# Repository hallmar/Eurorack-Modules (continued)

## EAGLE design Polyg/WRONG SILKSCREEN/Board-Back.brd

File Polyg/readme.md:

>ATTENTION BUILDERS THAT GOT THE FIRST BATCH OF 10 PCB'S(you can tell if they're part of that batch if they have no 'Version 1.1' written on them), THERE WAS A MAJOR ERROR IN THE SILKSCREEN DUE TO ME BEING AN IDIOT, SEE THE FOLDER CALLED 'WRONG SILKSCREEN' AND REFER TO THE 'BUILD MANUAL - WRONG SILKSCREEN' FOR CORRECT COMPONENT NUMBERING IN THE SCHEMATIC AND BOARD FILES FOR YOUR PCB VERSION

# Polyg 8-Voice Midi synth

# THIS PROJECT IS DISCONTINUED IN FAVOR OF V2 

[Youtube demo](https://www.youtube.com/watch?v=QhJZFhLLbBc&feature=youtu.be)

8 Voice polyphonic synthesizer with selectable Karplus strong(8 voice plucky string synth) or a 8 voice FM synth with square,sine,triangle and sawtooth. It has a basic FM(techincally Phase Modulation, like the DX7) with one Modulator. 
There's an index knob to set the ratio, decay for the operator and the amount of FM applied.

Current hardware uses a high quality 16bit/44.1kHz DAC(CD4334).

It has MIDI IN and MIDI OUT/THRU. It uses the Arturia Standard for DIN to stereo jack, so type B midi.
You can find adapters in almost every synthstore now. 

## Where/how to order
I won't have any PCB's in stock any time soon. This project is pretty much abandoned in favor of v2.
## Designed With

* Eagle CAD
* Arduino IDE
* Audio System Design Tool for Teensy Audio Library

## Versioning
* 1.0 - [Hardware] Original PCB batch with wrong silkscreen
* 1.1 - [Hardware] Current version of PCBs
* 1.0 - [Software] Original software release
## Authors

* **Hallmar Gauti Halldórsson** 

## License
Hardware: cc-by-sa-3.0

Software: MIT license

But if you want to sell or do something with the software or hardware then it'd be nice to include my name and link to my Github somewhere :)

## Acknowledgments
Alot of the inspiration for this project came from the [String Theory](https://makesynthsnotwar.com/modules/stringtheory/) eurorack module by Make Synths Not War.
The original String Theory was programmed by [Jan Ostman](https://janostman.wordpress.com).

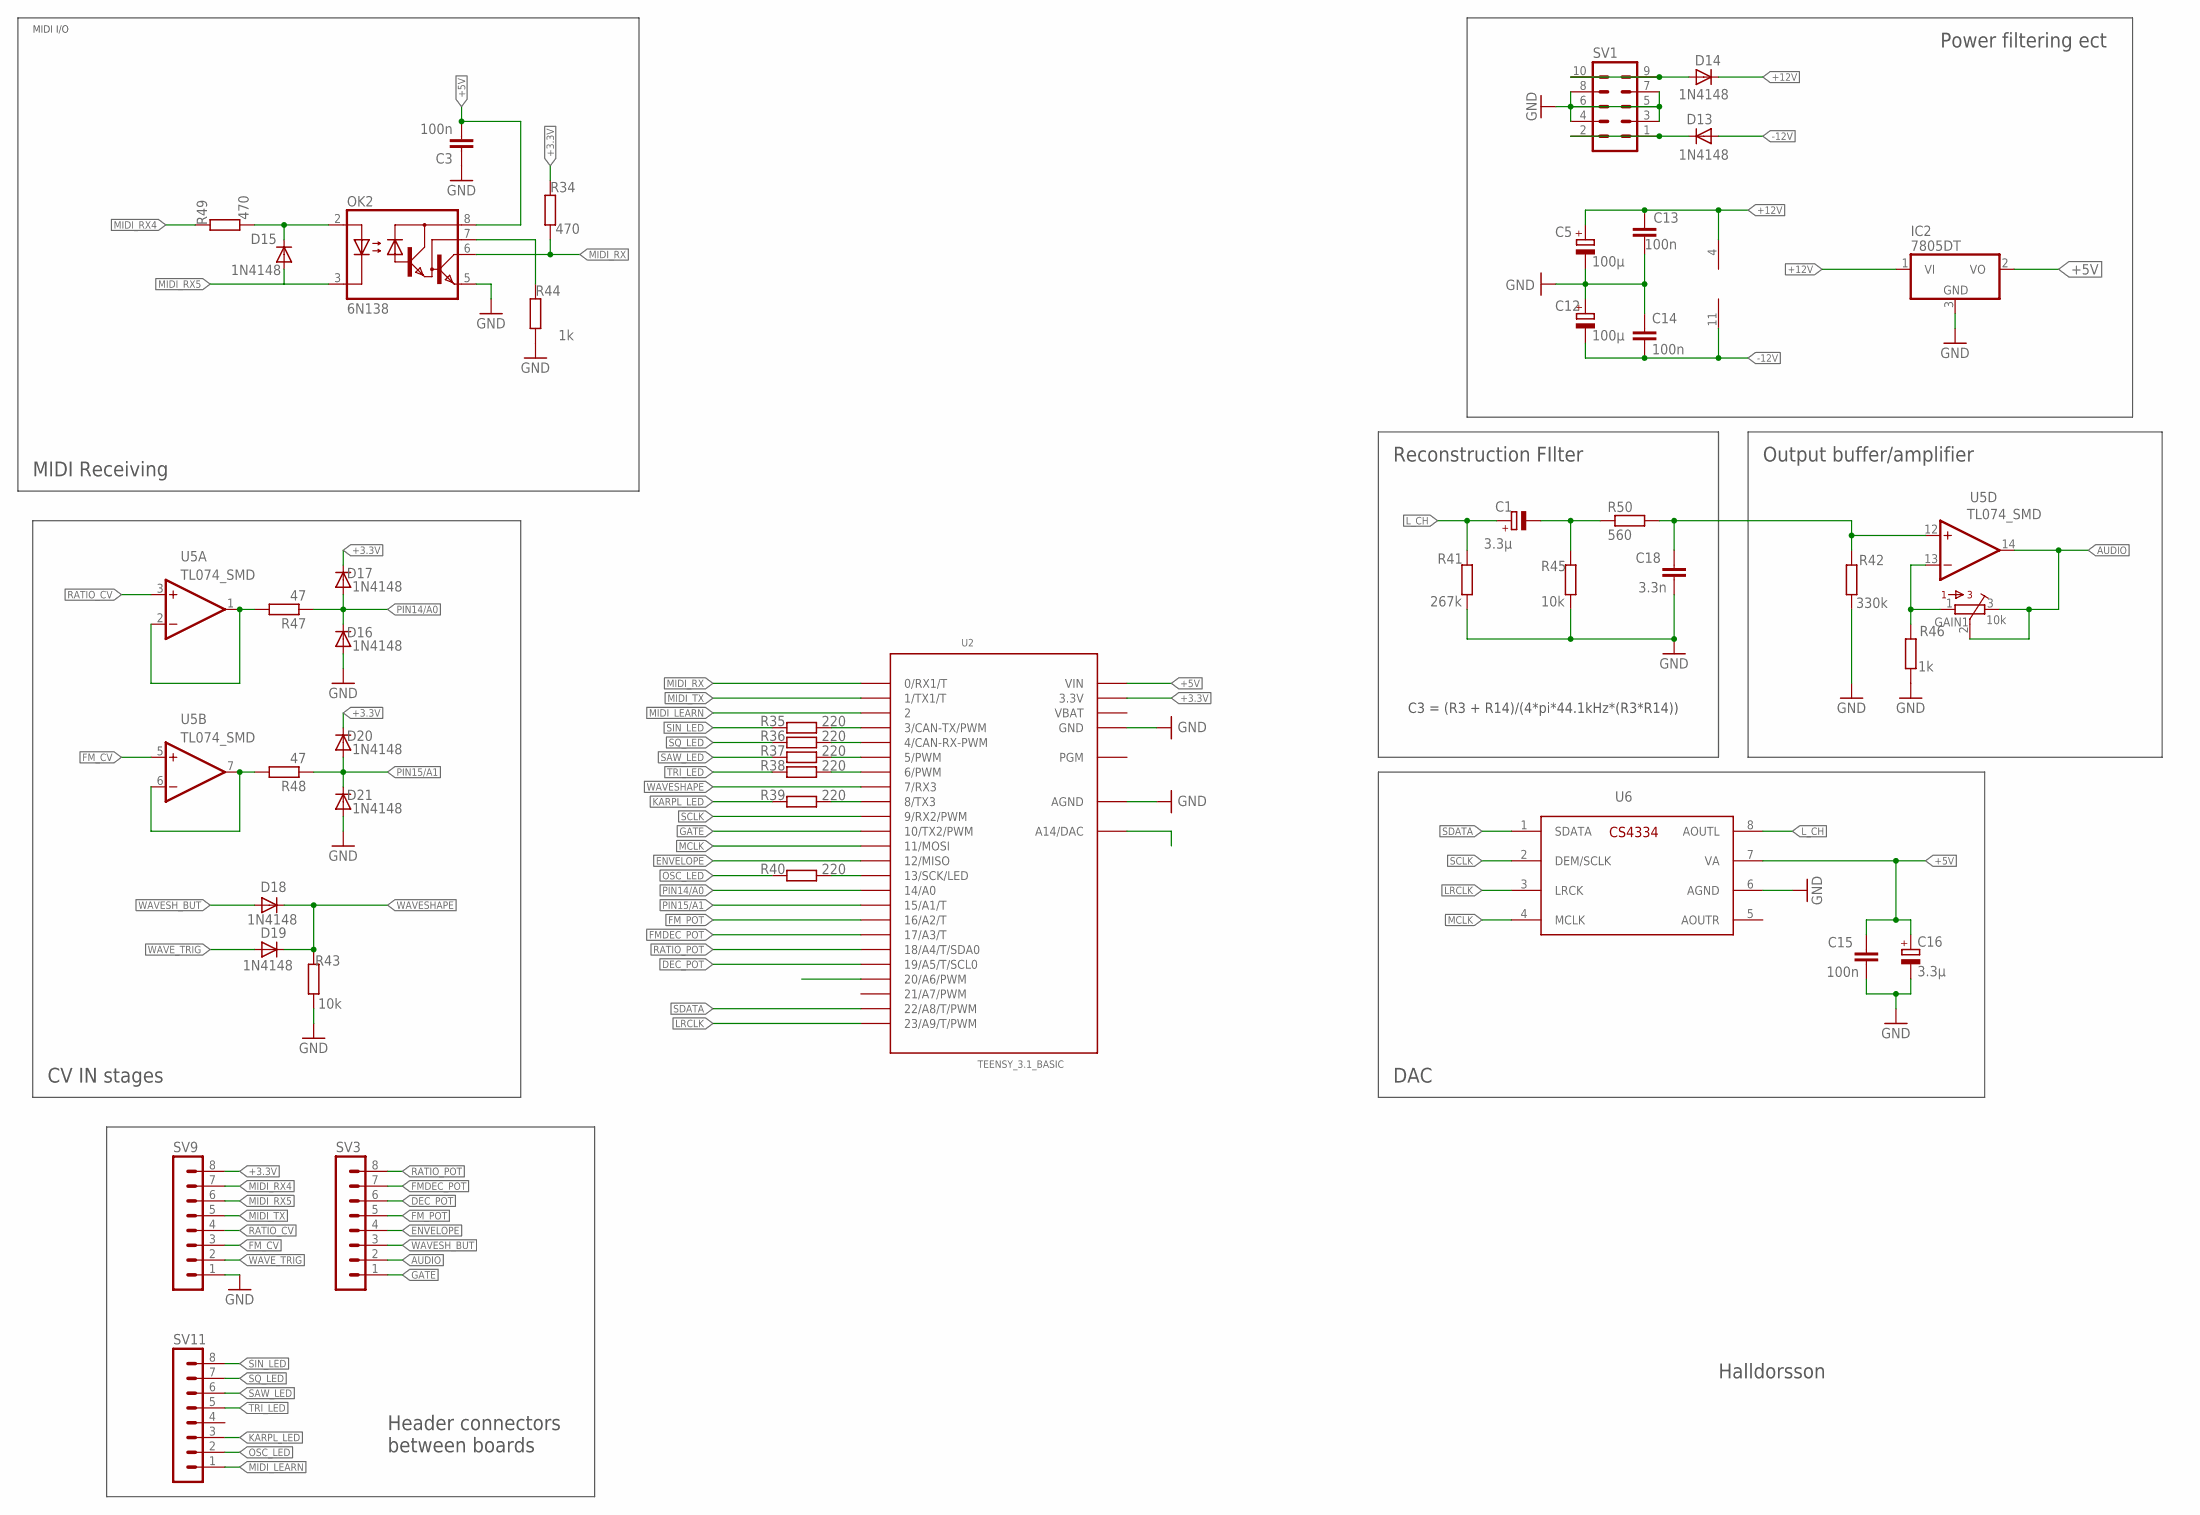
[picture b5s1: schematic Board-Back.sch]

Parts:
C1: 3.3µ; 153CLV-0405
C3, C13, C14, C15: 100n; C1206
C5, C12: 100µ; E5-6
C16: 3.3µ; 153CLV-0505
C18: 3.3n; C1206
D13, D14, D15, D16, D17, D18, D19, D20, D21: 1N4148; DO35-7
GAIN1: 10k; BOURNS_3362P_TRIMMER
IC2: 7805DT; TO252
OK2: 6N138; DIL08
R34, R49: 470; M1206
R35, R36, R37, R38, R39, R40: 220; M1206
R41: 267k; M1206
R42: 330k; M1206
R43, R45: 10k; M1206
R44, R46: 1k; M1206
R47, R48: 47; M1206
R50: 560; M1206
SV1: 10PIN_BACKSIDE
SV3, SV9, SV11: MA08-1
U2: TEENSY_3.1_BASIC
U5: TL074_SMD; SO14
U6: CS4334; SOIC127P600X175-8N

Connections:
+3.3V: D17.C, D20.C, R34.2, SV9.8, U2.3.3V, U2.3.3V1 (3.3V)
+5V: C3.2, C15.1, C16.+, IC2.2 (VO), OK2.8 (VCC), U2.VIN, U6.7 (VA)
+12V: C5.+, C13.1, D14.C, IC2.1 (VI), U5.4 (V+)
-12V: C12.-, C14.2, D13.A, U5.11 (V-)
AUDIO: GAIN1.2, GAIN1.3, SV3.2, U5.14 (OUT)
DEC_POT: SV3.6, U2.19/A5 (19/A5/T/SCL0)
ENVELOPE: SV3.4, U2.12 (12/MISO)
FMDEC_POT: SV3.7, U2.17/A3 (17/A3/T)
FM_CV: SV9.3, U5.5 (+IN)
FM_POT: SV3.5, U2.16/A2 (16/A2/T)
GATE: SV3.1, U2.10 (10/TX2/PWM)
GND: C3.1, C5.-, C12.+, C13.2, C14.1, C15.2, C16.-, C18.2, D16.A, D21.A, IC2.3 (GND), OK2.5 (GND), R41.2, R42.2, R43.1, R44.1, R45.2, R46.2, SV1.3, SV1.4, SV1.5, SV1.6, SV1.7, SV1.8, SV9.1, U2.AGND, U2.GND, U2.GND1 (GND), U6.6 (AGND)
KARPL_LED: R39.2, SV11.3
LRCLK: U2.23/A9 (23/A9/T/PWM), U6.3 (LRCK)
L_CH: C1.+, R41.1, U6.8 (AOUTL)
MCLK: U2.11 (11/MOSI), U6.4 (MCLK)
MIDI_LEARN: SV11.1, U2.2
MIDI_RX: OK2.6 (VO), R34.1, U2.0 (0/RX1/T)
MIDI_RX4: R49.2, SV9.7
MIDI_RX5: D15.A, OK2.3 (C), SV9.6
MIDI_TX: SV9.5, U2.1 (1/TX1/T)
unnamed: C1.-, R45.1, R50.1
unnamed: D13.C, SV1.1, SV1.2
unnamed: D15.C, OK2.2 (A), R49.1
unnamed: OK2.7 (VB), R44.2
unnamed: GAIN1.1, R46.1, U5.13 (-IN)
unnamed: D14.A, SV1.9, SV1.10
unnamed: R40.1, U2.13 (13/SCK/LED)
unnamed: C18.1, R42.1, R50.2, U5.12 (+IN)
unnamed: R35.1, U2.3 (3/CAN-TX/PWM)
unnamed: R36.1, U2.4 (4/CAN-RX-PWM)
unnamed: R37.1, U2.5 (5/PWM)
unnamed: R48.2, U5.6 (-IN), U5.7 (OUT)
unnamed: R47.2, U5.1 (OUT), U5.2 (-IN)
unnamed: R38.1, U2.6 (6/PWM)
unnamed: R39.1, U2.8 (8/TX3)
OSC_LED: R40.2, SV11.2
PIN14/A0: D16.C, D17.A, R47.1, U2.14/A0
PIN15/A1: D20.A, D21.C, R48.1, U2.15/A1 (15/A1/T)
RATIO_CV: SV9.4, U5.3 (+IN)
RATIO_POT: SV3.8, U2.18/A4 (18/A4/T/SDA0)
SAW_LED: R37.2, SV11.6
SCLK: U2.9 (9/RX2/PWM), U6.2 (DEM/SCLK)
SDATA: U2.22/A8 (22/A8/T/PWM), U6.1 (SDATA)
SIN_LED: R35.2, SV11.8
SQ_LED: R36.2, SV11.7
TRI_LED: R38.2, SV11.5
VBAT: U2.VBAT
WAVESHAPE: D18.C, D19.C, R43.2, U2.7 (7/RX3)
WAVESH_BUT: D18.A, SV3.3
WAVE_TRIG: D19.A, SV9.2

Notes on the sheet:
MIDI I/O
Halldorsson
DAC
Reconstruction FIlter
CV IN stages
Header connectors between boards
MIDI Receiving
Power filtering ect
Output buffer/amplifier
C3 = (R3 + R14)/(4*pi*44.1kHz*(R3*R14))

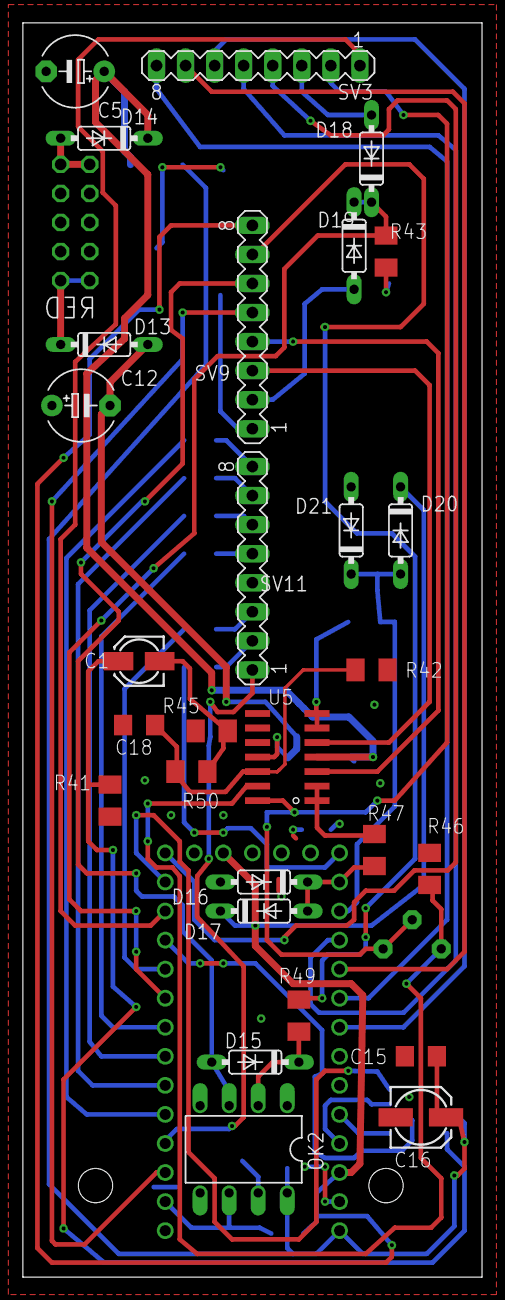
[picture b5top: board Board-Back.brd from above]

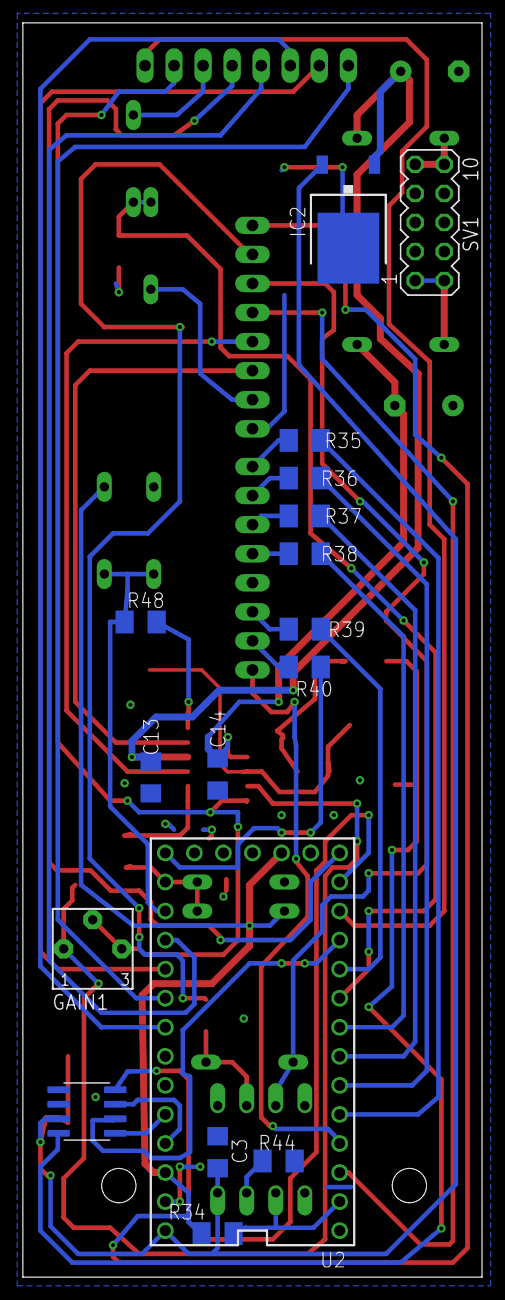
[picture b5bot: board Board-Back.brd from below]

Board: 2 copper layers, 40.1 x 109.7 mm, 45 parts (16 on the bottom side), 50 nets.

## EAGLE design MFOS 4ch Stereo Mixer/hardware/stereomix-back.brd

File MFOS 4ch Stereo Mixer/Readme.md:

# Music From Outer Space 4 channel Stereo mixer 
It's simple.
It's a 4 channel stereo in and one stereo out mixer.
Has 1 attenuator per channel, the left jack is normalled to the right(if you only plug a jack into the left then the signal at the left jack is passed to the right channel too).

[original schematic](http://musicfromouterspace.com/analogsynth_new/HOT_TIPS/PDF/simple_stereo_summer_assembly.pdf)

## Where/how to order
Not selling any PCB's for this one. It's only for open source/documentation purposes.

## Designed With

* Eagle CAD

## Versioning

## Authors

* PCB design by **Hallmar Gauti Halldórsson** 
* Original Schematic design by the late **Ray Wilson of Music From Outer Space**

## License
Hardware: cc-by-sa-3.0

## Acknowledgments
The design of the circuit was completely done by the great Ray Wilson of [Music From Outer Space](http://musicfromouterspace.com).
I merely designed the frontpanel and PCB for it for Eurorack. Here is the [original schematic](http://musicfromouterspace.com/analogsynth_new/HOT_TIPS/PDF/simple_stereo_summer_assembly.pdf)

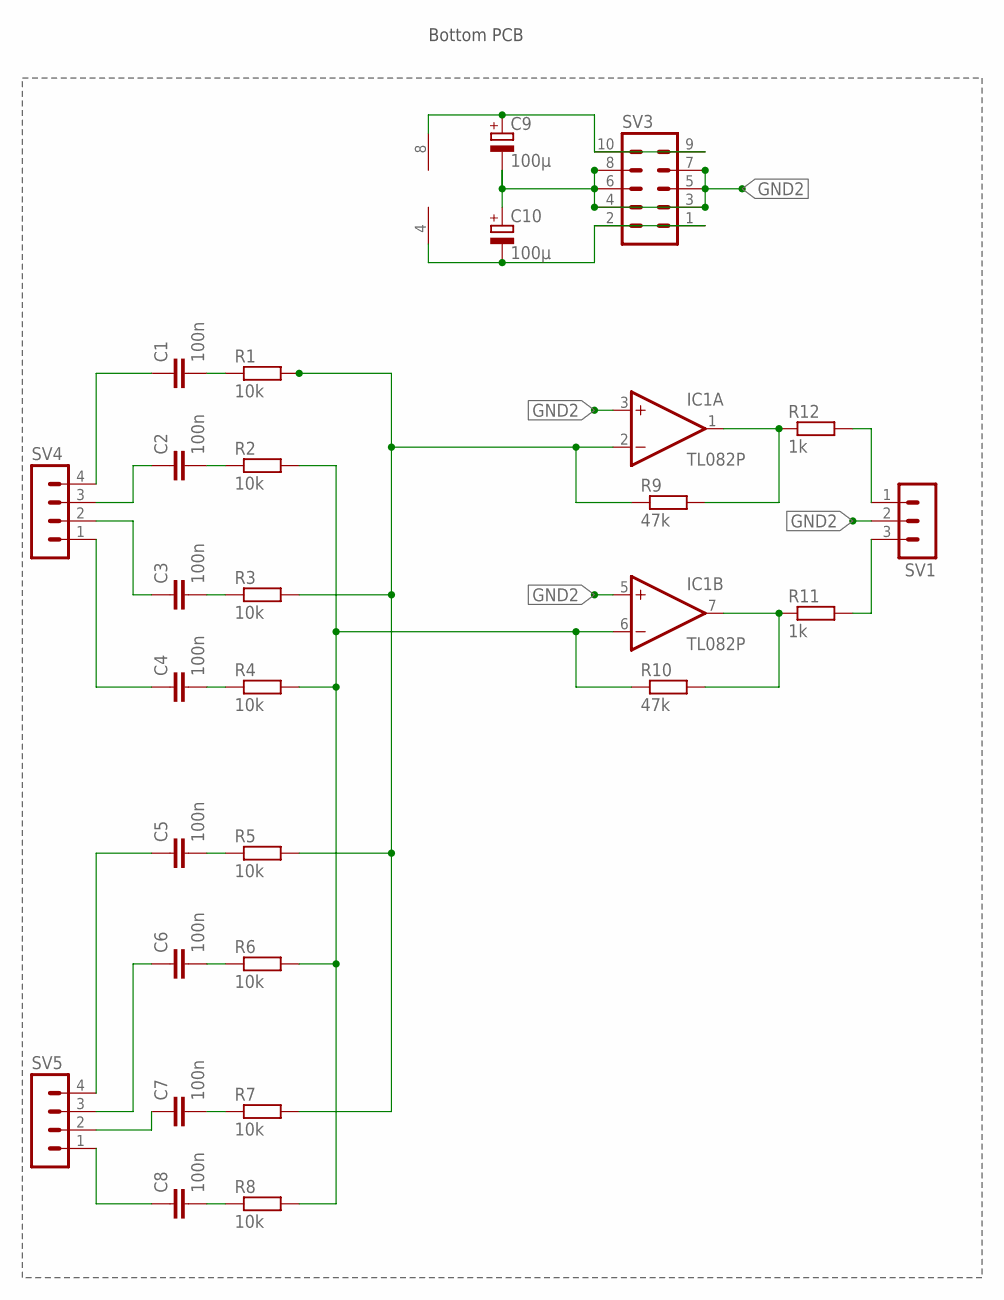
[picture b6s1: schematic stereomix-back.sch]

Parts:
C1, C2, C3, C4, C5, C6, C7, C8: 100n; C050-024X044
C9: 100µ; E2,5-6
C10: 100µ; E2,5-6E
IC1: TL082P; DIL08
R1, R2, R3, R4, R5, R6, R7, R8: 10k; 0204/7
R9, R10: 47k; 0204/7
R11, R12: 1k; 0204/7
SV1: MA03-1
SV3: MA05-2
SV4, SV5: MA04-1

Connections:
GND2: C9.-, C10.+, IC1.3 (+IN), IC1.5 (+IN), SV1.2, SV3.3, SV3.4, SV3.5, SV3.6, SV3.7, SV3.8
unnamed: IC1.2 (-IN), R1.2, R3.2, R5.2, R7.2, R9.1
unnamed: IC1.1 (OUT), R9.2, R12.1
unnamed: IC1.7 (OUT), R10.2, R11.1
unnamed: IC1.6 (-IN), R2.2, R4.2, R6.2, R8.2, R10.1
unnamed: R12.2, SV1.1
unnamed: C1.2, R1.1
unnamed: C2.2, R2.1
unnamed: C3.2, R3.1
unnamed: C4.2, R4.1
unnamed: C5.2, R5.1
unnamed: C6.2, R6.1
unnamed: C7.2, R7.1
unnamed: C8.2, R8.1
unnamed: R11.2, SV1.3
unnamed: C9.+, IC1.8 (V+), SV3.9, SV3.10
unnamed: C10.-, IC1.4 (V-), SV3.1, SV3.2
unnamed: C8.1, SV5.1
unnamed: C7.1, SV5.2
unnamed: C6.1, SV5.3
unnamed: C5.1, SV5.4
unnamed: C4.1, SV4.1
unnamed: C3.1, SV4.2
unnamed: C2.1, SV4.3
unnamed: C1.1, SV4.4

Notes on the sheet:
Bottom PCB

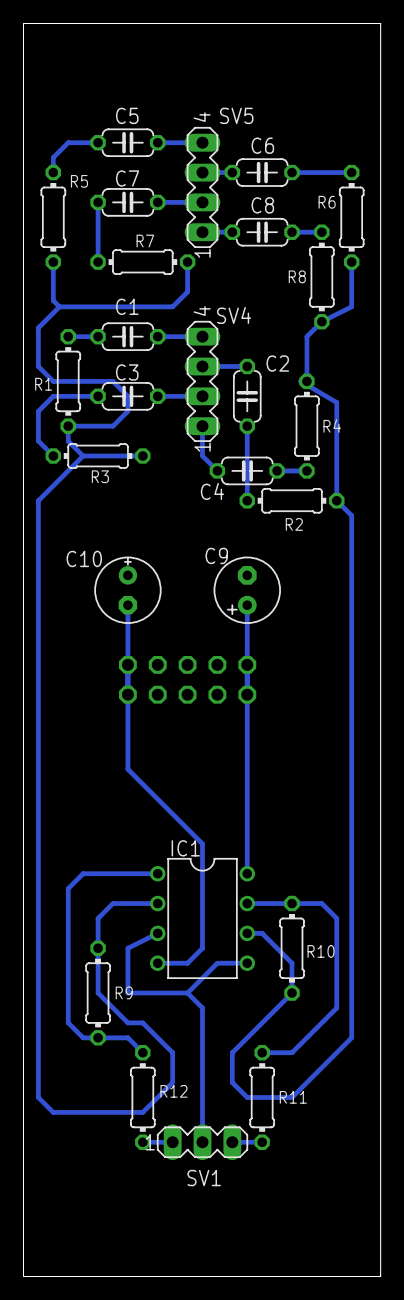
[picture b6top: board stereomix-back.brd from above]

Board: 2 copper layers, 30.4 x 106.7 mm, 27 parts (1 on the bottom side), 25 nets.

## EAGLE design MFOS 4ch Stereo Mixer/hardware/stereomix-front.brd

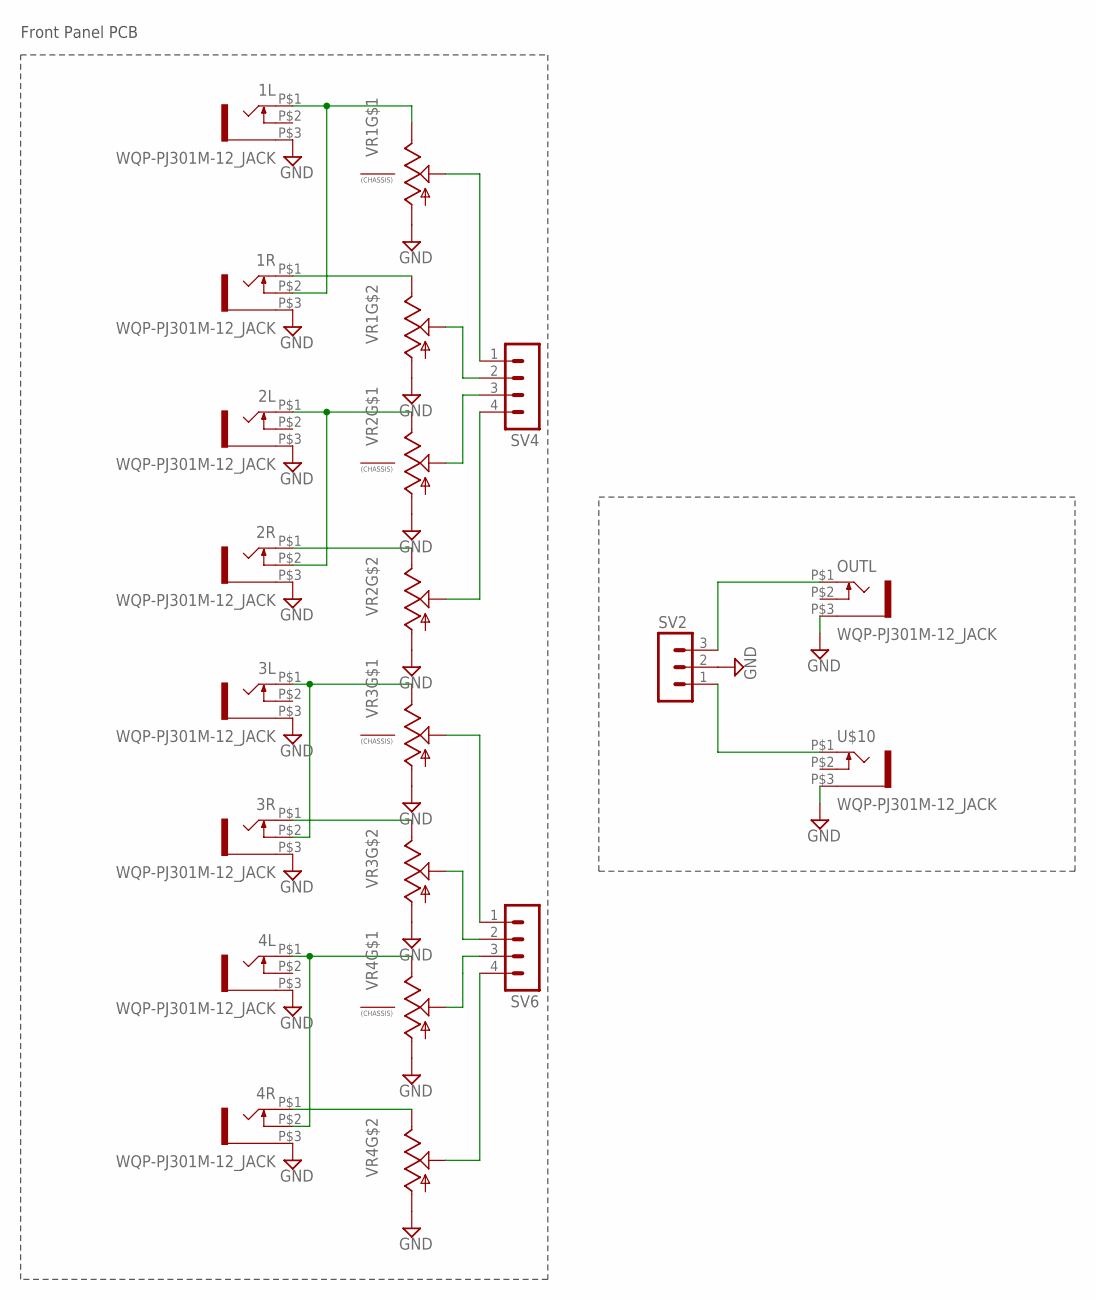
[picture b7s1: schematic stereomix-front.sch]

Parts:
1L, 1R, 2L, 2R, 3L, 3R, 4L, 4R: WQP-PJ301M-12_JACK
OUTL: WQP-PJ301M-12_JACK
SV2: MA03-1
SV4, SV6: MA04-1
U$10: WQP-PJ301M-12_JACK
VR1, VR2, VR3, VR4: ALPHA-9MM-DUALPOT; DUAL_9MM_SNAP-IN_POT

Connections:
GND: 1L.P$3 (1), 1R.P$3 (1), 2L.P$3 (1), 2R.P$3 (1), 3L.P$3 (1), 3R.P$3 (1), 4L.P$3 (1), 4R.P$3 (1), OUTL.P$3 (1), SV2.2, U$10.P$3 (1), VR1.1 (A), VR1.1B (A), VR2.1 (A), VR2.1B (A), VR3.1 (A), VR3.1B (A), VR4.1 (A), VR4.1B (A)
unnamed: SV4.1, VR1.2 (S)
unnamed: SV4.2, VR1.2B (S)
unnamed: SV4.3, VR2.2 (S)
unnamed: SV4.4, VR2.2B (S)
unnamed: SV6.1, VR3.2 (S)
unnamed: SV6.2, VR3.2B (S)
unnamed: 1L.P$1 (2), 1R.P$2 (3), VR1.3 (E)
unnamed: 1R.P$1 (2), VR1.3B (E)
unnamed: 2L.P$1 (2), 2R.P$2 (3), VR2.3 (E)
unnamed: 2R.P$1 (2), VR2.3B (E)
unnamed: 3L.P$1 (2), 3R.P$2 (3), VR3.3 (E)
unnamed: 3R.P$1 (2), VR3.3B (E)
unnamed: 4L.P$1 (2), 4R.P$2 (3), VR4.3 (E)
unnamed: 4R.P$1 (2), VR4.3B (E)
unnamed: OUTL.P$1 (2), SV2.3
unnamed: SV2.1, U$10.P$1 (2)
unnamed: SV6.3, VR4.2 (S)
unnamed: SV6.4, VR4.2B (S)

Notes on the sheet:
Front Panel PCB

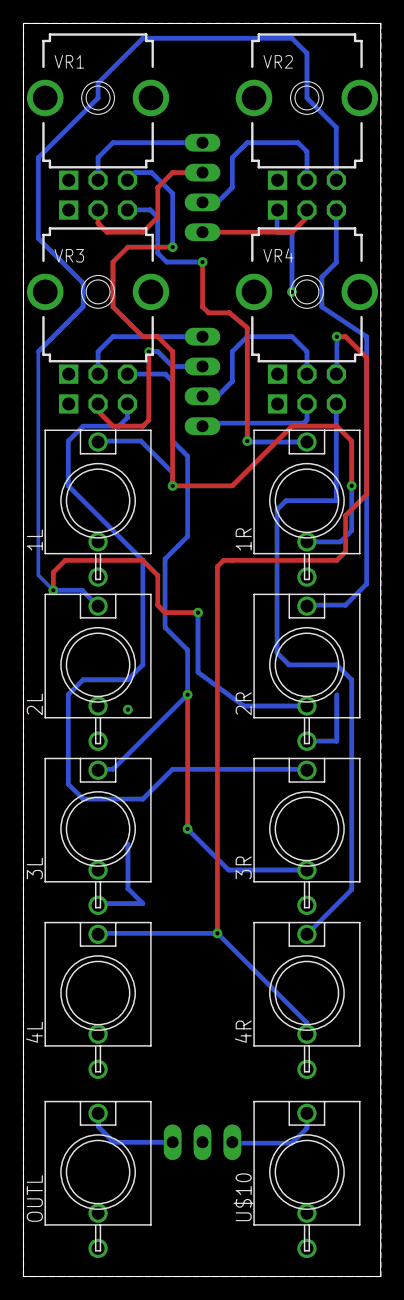
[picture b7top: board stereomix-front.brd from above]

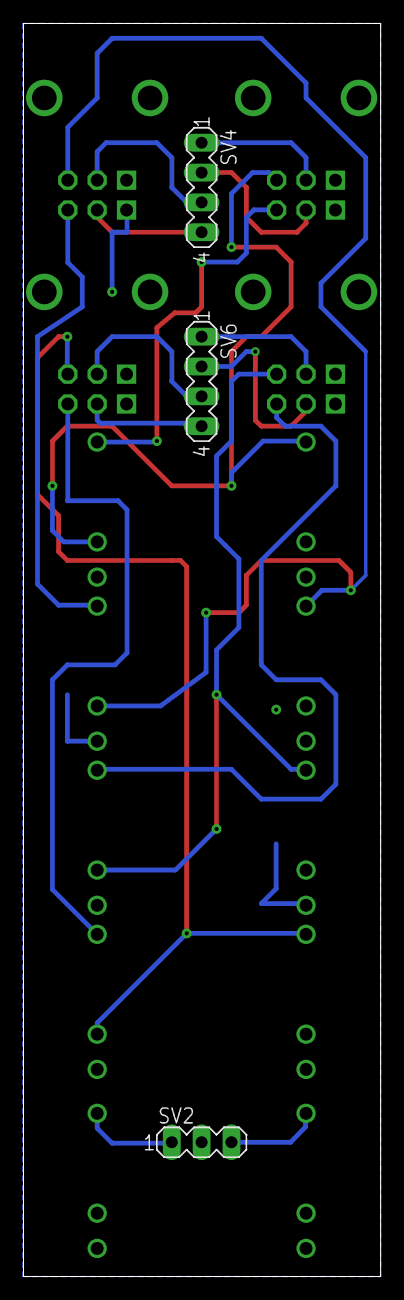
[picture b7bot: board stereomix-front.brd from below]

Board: 2 copper layers, 30.4 x 106.7 mm, 17 parts (3 on the bottom side), 19 nets.

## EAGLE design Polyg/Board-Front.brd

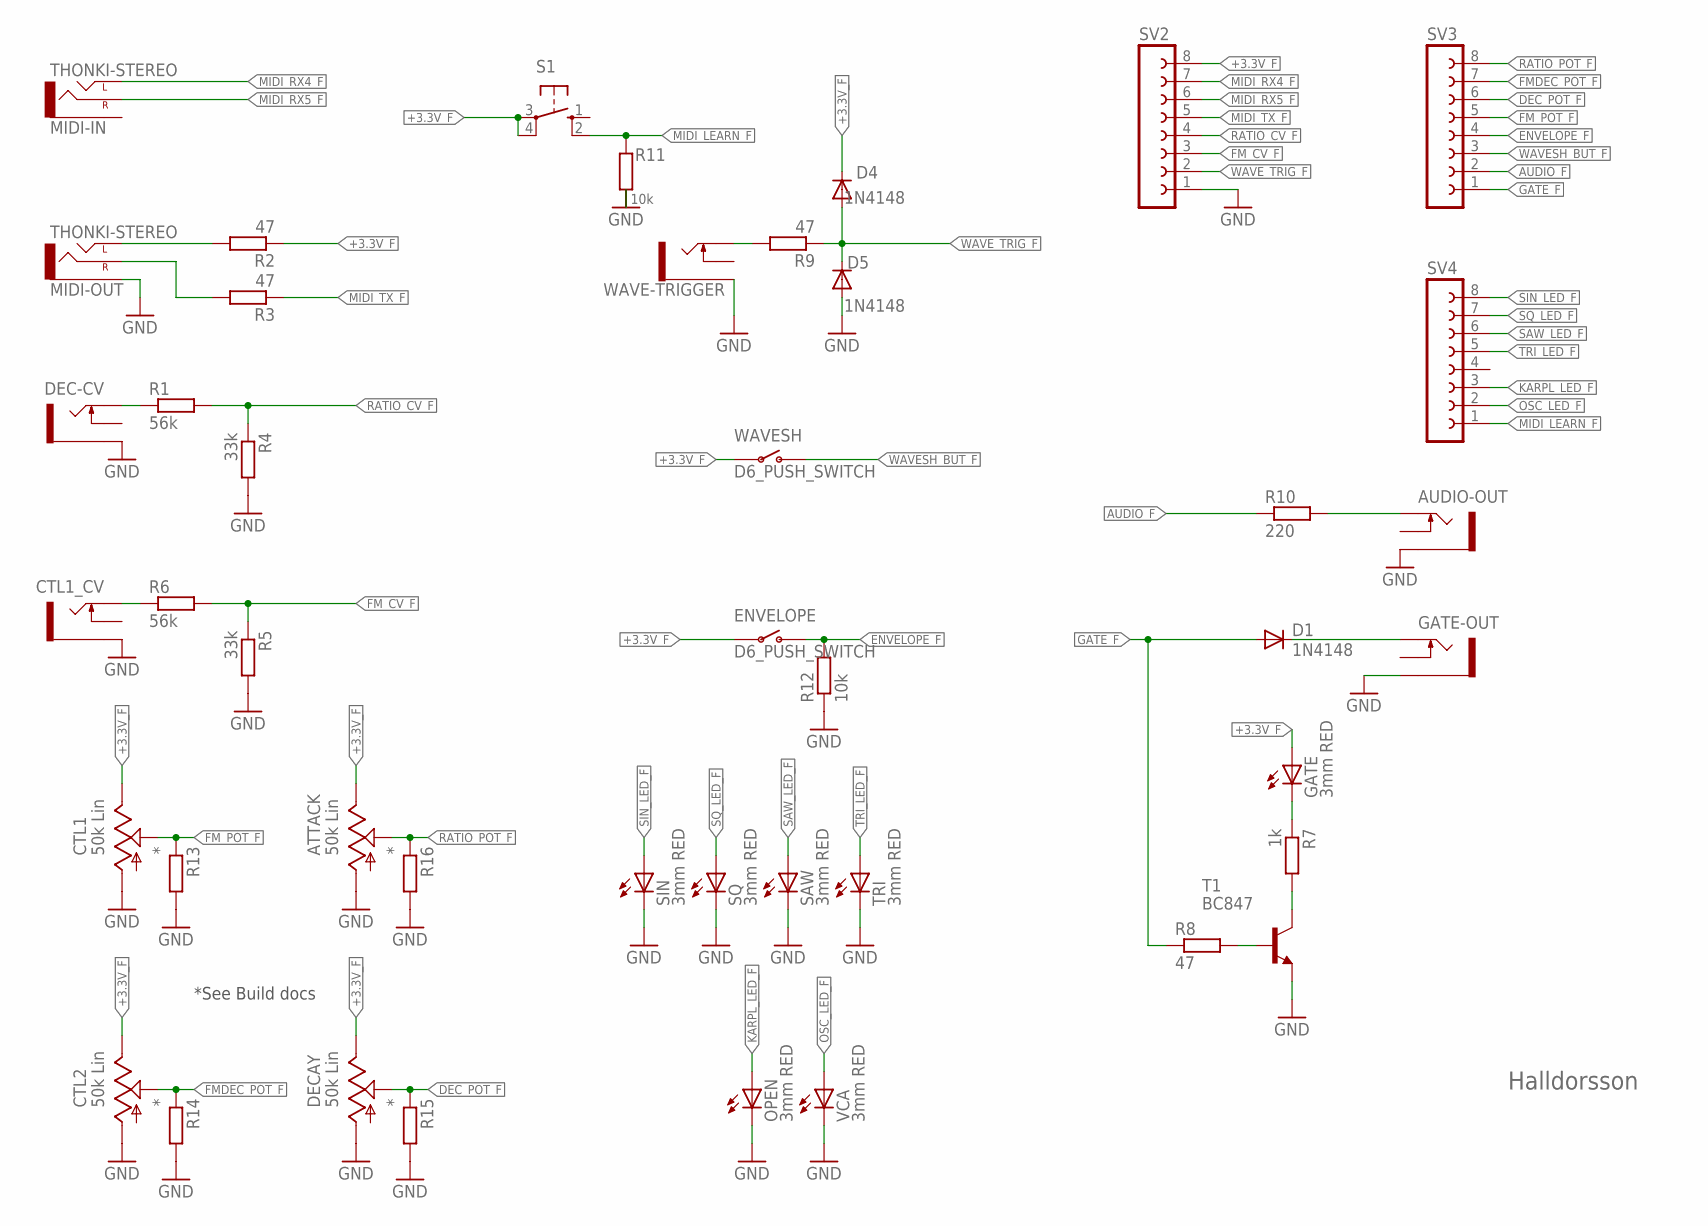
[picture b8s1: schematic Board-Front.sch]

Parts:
ATTACK: 50k Lin; 9MM_SNAP-IN_POT
AUDIO-OUT: THONKICONNNEW; WQP-PJ301M-12_JACK
CTL1, CTL2: 50k Lin; 9MM_SNAP-IN_POT
CTL1_CV: THONKICONNNEW; WQP-PJ301M-12_JACK
D1, D4, D5: 1N4148; DO35-7
DEC-CV: THONKICONNNEW; WQP-PJ301M-12_JACK
DECAY: 50k Lin; 9MM_SNAP-IN_POT
ENVELOPE: D6_PUSH_SWITCH
GATE: 3mm RED; LED3MM
GATE-OUT: THONKICONNNEW; WQP-PJ301M-12_JACK
MIDI-IN: THONKI-STEREO; WQP-PJ366ST_JACK
MIDI-OUT: THONKI-STEREO; WQP-PJ366ST_JACK
OPEN: 3mm RED; LED3MM
R1, R6: 56k; M1206
R2, R3, R8, R9: 47; M1206
R4, R5: 33k; M1206
R7: 1k; M1206
R10: 220; M1206
R11, R12: 10k; M1206
R13, R14, R15, R16: *; M1206
S1: 10-XX; B3F-10XX
SAW: 3mm RED; LED3MM
SIN: 3mm RED; LED3MM
SQ: 3mm RED; LED3MM
SV2, SV3, SV4: FE08-1; FE08
T1: BC847; SOT23
TRI: 3mm RED; LED3MM
VCA: 3mm RED; LED3MM
WAVE-TRIGGER: THONKICONNNEW; WQP-PJ301M-12_JACK
WAVESH: D6_PUSH_SWITCH

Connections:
+3.3V_F: ATTACK.3 (E), CTL1.3 (E), CTL2.3 (E), D4.C, DECAY.3 (E), ENVELOPE.P$3, ENVELOPE.P$4, GATE.A, R2.1, S1.3, S1.4 (P1), SV2.8, WAVESH.P$3, WAVESH.P$4
AUDIO_F: R10.1, SV3.2
B: R8.2, T1.1 (B)
C: R7.2, T1.3 (C)
DEC_POT_F: DECAY.2 (S), R15.1, SV3.6
ENVELOPE_F: ENVELOPE.P$1 (O), ENVELOPE.P$2 (O), R12.2, SV3.4
FMDEC_POT_F: CTL2.2 (S), R14.1, SV3.7
FM_CV_F: R5.1, R6.2, SV2.3
FM_POT_F: CTL1.2 (S), R13.1, SV3.5
GATE_F: D1.A, R8.1, SV3.1
GND: ATTACK.1 (A), AUDIO-OUT.P$3_SLEEVE (SLEEVE), CTL1.1 (A), CTL1_CV.P$3_SLEEVE (SLEEVE), CTL2.1 (A), D5.A, DEC-CV.P$3_SLEEVE (SLEEVE), DECAY.1 (A), GATE-OUT.P$3_SLEEVE (SLEEVE), MIDI-OUT.P$3_SLEEVE (SLEEVE), OPEN.K (C), R4.2, R5.2, R11.2, R12.1, R13.2, R14.2, R15.2, R16.2, SAW.K (C), SIN.K (C), SQ.K (C), SV2.1, T1.2 (E), TRI.K (C), VCA.K (C), WAVE-TRIGGER.P$3_SLEEVE (SLEEVE)
KARPL_LED_F: OPEN.A, SV4.3
MIDI_LEARN_F: R11.1, S1.2 (S1), SV4.1
MIDI_RX4_F: MIDI-IN.P$1_TIP (LEFT), SV2.7
MIDI_RX5_F: MIDI-IN.P$2_SWITCH (RIGHT), SV2.6
MIDI_TX_F: R3.1, SV2.5
unnamed: DEC-CV.P$1_TIP (TIP), R1.1
unnamed: GATE.K (C), R7.1
unnamed: D1.C, GATE-OUT.P$1_TIP (TIP)
unnamed: CTL1_CV.P$1_TIP (TIP), R6.1
unnamed: AUDIO-OUT.P$1_TIP (TIP), R10.2
unnamed: MIDI-OUT.P$2_SWITCH (RIGHT), R3.2
unnamed: MIDI-OUT.P$1_TIP (LEFT), R2.2
unnamed: R9.2, WAVE-TRIGGER.P$1_TIP (TIP)
OSC_LED_F: SV4.2, VCA.A
RATIO_CV_F: R1.2, R4.1, SV2.4
RATIO_POT_F: ATTACK.2 (S), R16.1, SV3.8
SAW_LED_F: SAW.A, SV4.6
SIN_LED_F: SIN.A, SV4.8
SQ_LED_F: SQ.A, SV4.7
TRI_LED_F: SV4.5, TRI.A
WAVESH_BUT_F: SV3.3, WAVESH.P$1 (O), WAVESH.P$2 (O)
WAVE_TRIG_F: D4.A, D5.C, R9.1, SV2.2

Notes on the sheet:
*See Build docs
Halldorsson

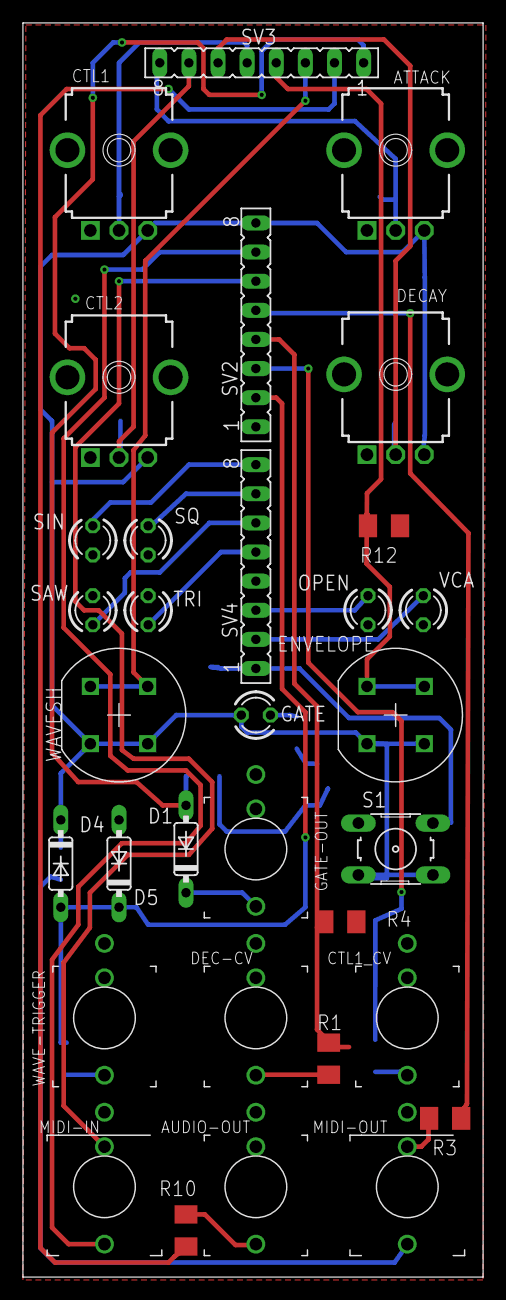
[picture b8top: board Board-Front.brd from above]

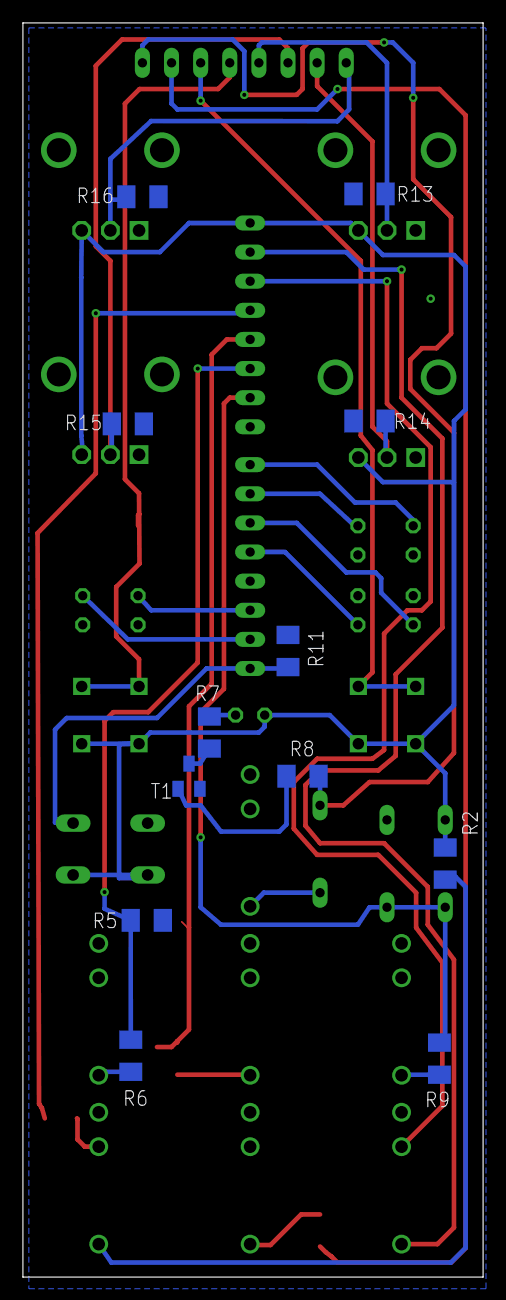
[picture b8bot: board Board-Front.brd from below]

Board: 2 copper layers, 40.1 x 109.4 mm, 44 parts (12 on the bottom side), 33 nets.

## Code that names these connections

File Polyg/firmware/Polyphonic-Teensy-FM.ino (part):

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
//----Outputs----------
const short gate_o = 10;
const short sin_led = 3;
const short sq_led = 4;
const short saw_led = 5;
const short tri_led = 6;
const short string_led = 8;
const short osc_led = 13;

//----Inputs-------------
const short waveshape = 7;
const short envelope = 12;
const short midi_learn = 2;
Bounce wavesh_but = Bounce();
Bounce envel_but = Bounce();
Bounce midilearn_but = Bounce();
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{
  
  AudioMemory(80);
  pinMode(sin_led, OUTPUT);
  pinMode(sq_led, OUTPUT);
  pinMode(saw_led, OUTPUT);
  pinMode(tri_led, OUTPUT);
  pinMode(string_led, OUTPUT);
  pinMode(osc_led, OUTPUT);
  pinMode(gate_o, OUTPUT);
  
  digitalWrite(sin_led, HIGH);
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  digitalWrite(string_led, LOW);
  digitalWrite(osc_led, HIGH);
  
  pinMode(waveshape, INPUT);
  pinMode(envelope, INPUT);
  pinMode(midi_learn, INPUT);
  
  wavesh_but.attach(waveshape);
  wavesh_but.interval(debounce);
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
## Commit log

2018-11-12 Create Polyg
2020-09-20 deleted badly designed polyg v1
2020-09-20 add images
2020-11-19 endurnefna möppu
2020-11-19 endurnefna pdf
2020-11-20 möppubreytingar
2020-11-29 setja inn ókláraða útgáfu af firmware og hardware
2020-11-30 breyta um mynd
2020-12-24 upload pdf
2020-12-25 breyta mynd
2020-12-25 uppfæra mynd
2021-01-19 upddate to KICAD
2021-01-19 updatepdf
2021-01-19 updatepdffolder
2021-02-19 update frontpanel
2023-01-03 change version
2023-01-03 put up new version of Fjöl on Github
2023-01-19 change folder name
